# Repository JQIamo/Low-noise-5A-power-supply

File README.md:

# Low-noise-5A-power-supply
5A low noise +-15 V power supply for Eurocard boxes

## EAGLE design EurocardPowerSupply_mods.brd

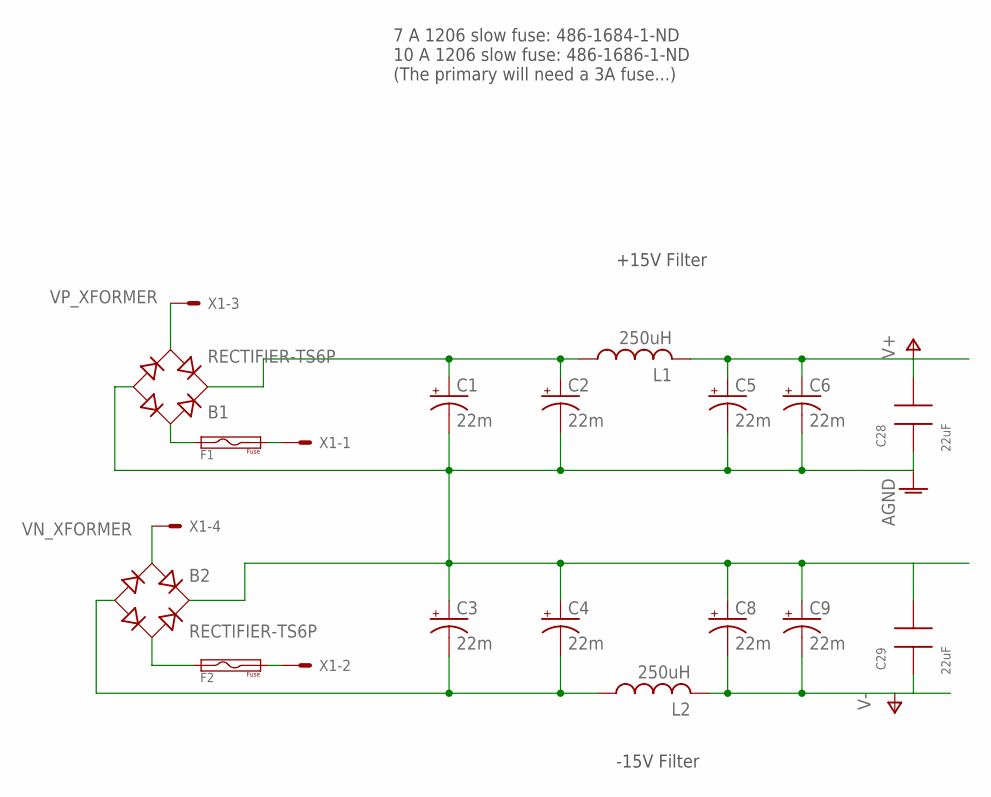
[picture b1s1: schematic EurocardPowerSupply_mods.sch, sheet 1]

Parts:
B1, B2: RECTIFIER-TS6P; TS6P
C1, C2, C3, C4, C5, C6, C8, C9: 22m; EB35D
C28, C29: 22uF; 1206; DIGIKEY 445-8045-1-ND
F1, F2: FUSE1206; DIGIKEY 486-1686-1-ND
L1, L2: 250uH; 5721-RC
X1: 5566-4

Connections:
AGND: B1.-, B2.+, C1.-, C2.-, C3.+, C4.+, C5.-, C6.-, C8.+, C9.+, C28.1, C29.2; also elsewhere on the board
unnamed: B1.AC1, F1.1
unnamed: F1.2, X1.1
unnamed: F2.2, X1.2
unnamed: B2.AC2, F2.1
V+: C5.+, C6.+, C28.2, L1.P$2 (2); also elsewhere on the board
V-: C8.-, C9.-, C29.1, L2.P$2 (2); also elsewhere on the board
VN_RECT: B2.-, C3.-, C4.-, L2.P$1 (1); also elsewhere on the board
VN_XFORMER: B2.AC1, X1.4
VP_RECT: B1.+, C1.+, C2.+, L1.P$1 (1); also elsewhere on the board
VP_XFORMER: B1.AC2, X1.3

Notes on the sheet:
-15V Filter
+15V Filter
7 A 1206 slow fuse: 486-1684-1-ND 10 A 1206 slow fuse: 486-1686-1-ND (The primary will need a 3A fuse...)

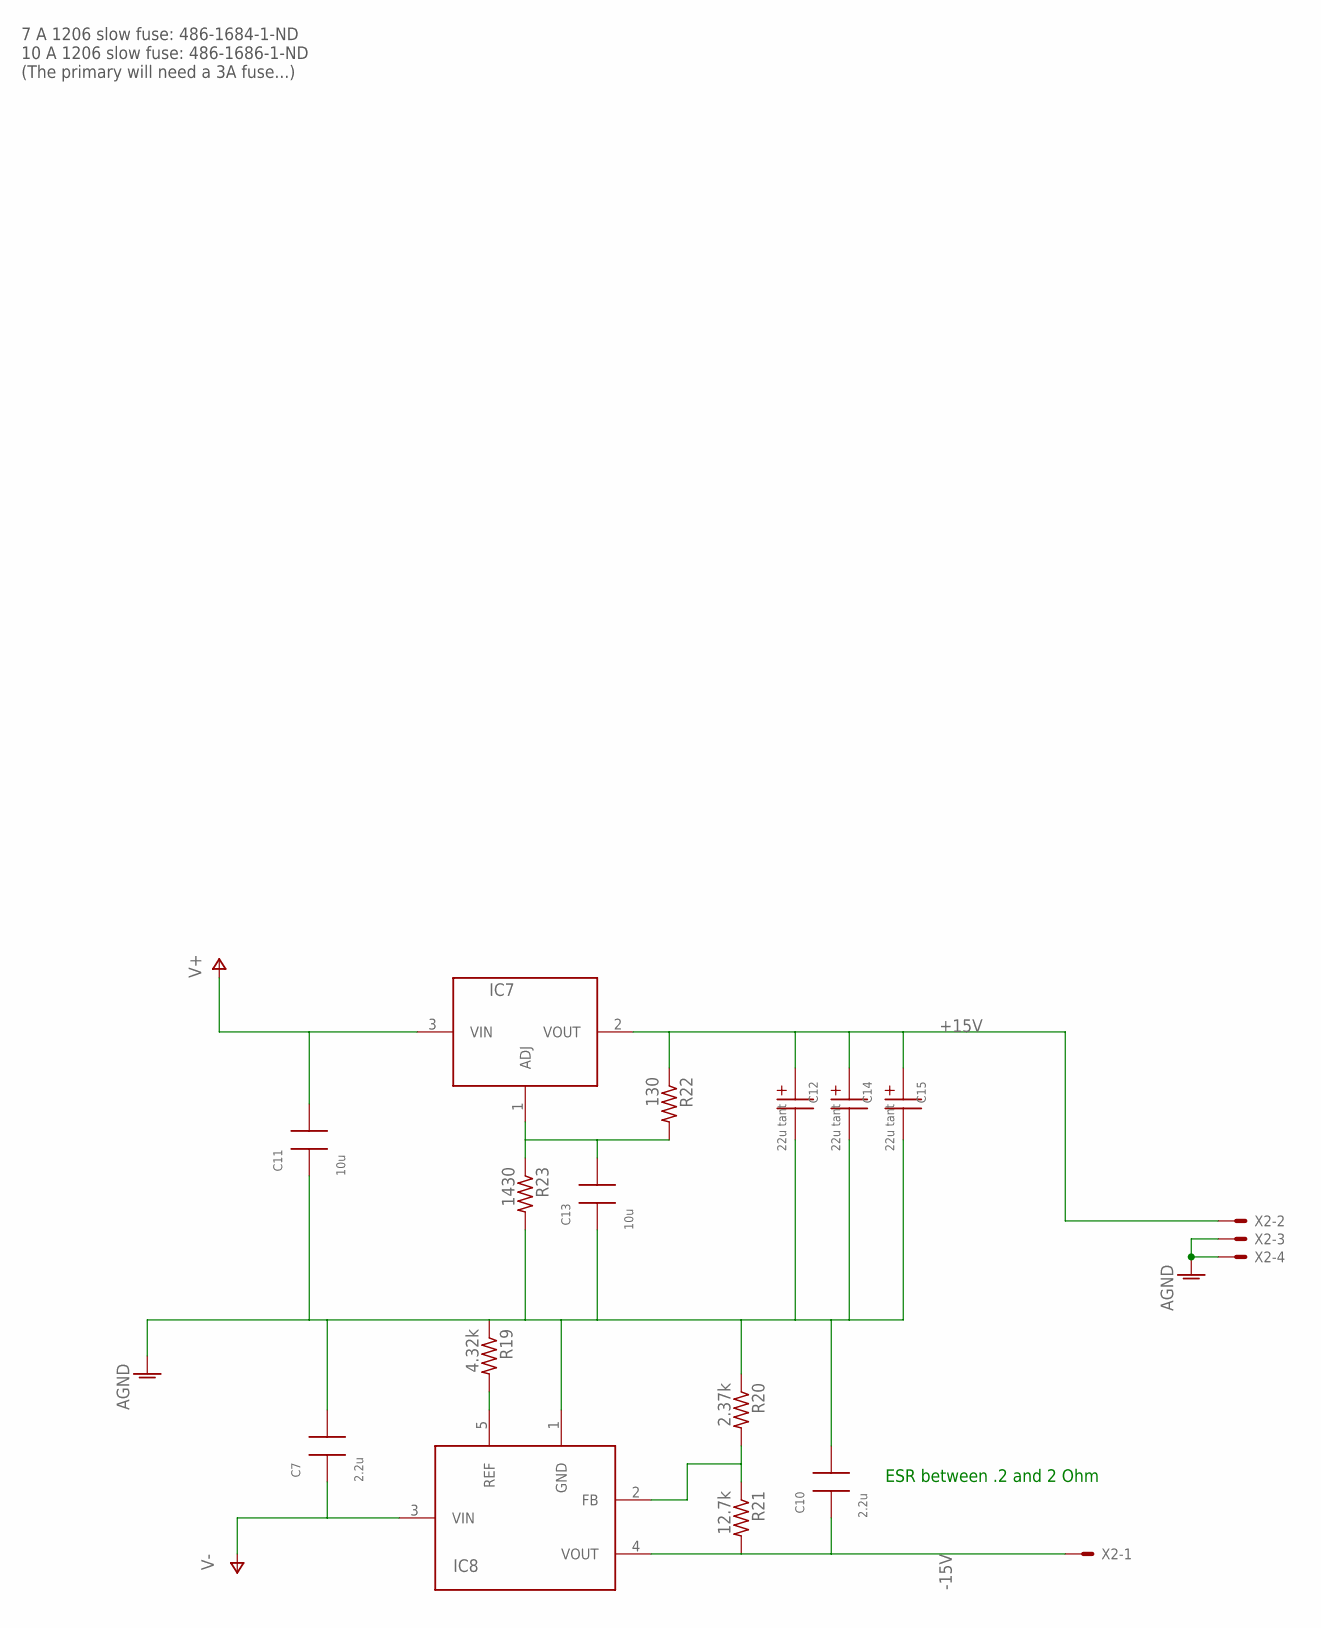
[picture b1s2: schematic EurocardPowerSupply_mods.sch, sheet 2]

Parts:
C7, C10: 2.2u; 1206; DIGIKEY 399-1249-1-ND
C11, C13: 10u; 1206; DIGIKEY 399-1249-1-ND
C12, C14, C15: 22u tant; 1206P; DIGIKEY 399-1249-1-ND
IC7: LM1084TO220; T03B
IC8: LT1185TO220/INLINE; T05A
R19: 4.32k; R1206; DIGIKEY 541-1.5KECT-ND
R20: 2.37k; R1206; DIGIKEY 541-1.5KECT-ND
R21: 12.7k; R1206; DIGIKEY 541-1.5KECT-ND
R22: 130; R1206; DIGIKEY 541-1.5KECT-ND
R23: 1430; R1206; DIGIKEY 541-1.5KECT-ND
X2: 5566-4

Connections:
+15V: C12.1, C14.1, C15.1, IC7.2 (VOUT), R22.1, X2.2
-15V: C10.1, IC8.4 (VOUT), R21.2, X2.1
AGND: C7.2, C10.2, C11.1, C12.2, C13.1, C14.2, C15.2, IC8.1 (GND), R19.1, R20.1, R23.2, X2.3, X2.4; also elsewhere on the board
unnamed: IC8.2 (FB), R20.2, R21.1
unnamed: C13.2, IC7.1 (ADJ), R22.2, R23.1
unnamed: IC8.5 (REF), R19.2
V+: C11.2, IC7.3 (VIN); also elsewhere on the board
V-: C7.1, IC8.3 (VIN); also elsewhere on the board

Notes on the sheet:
7 A 1206 slow fuse: 486-1684-1-ND 10 A 1206 slow fuse: 486-1686-1-ND (The primary will need a 3A fuse...)
ESR between .2 and 2 Ohm

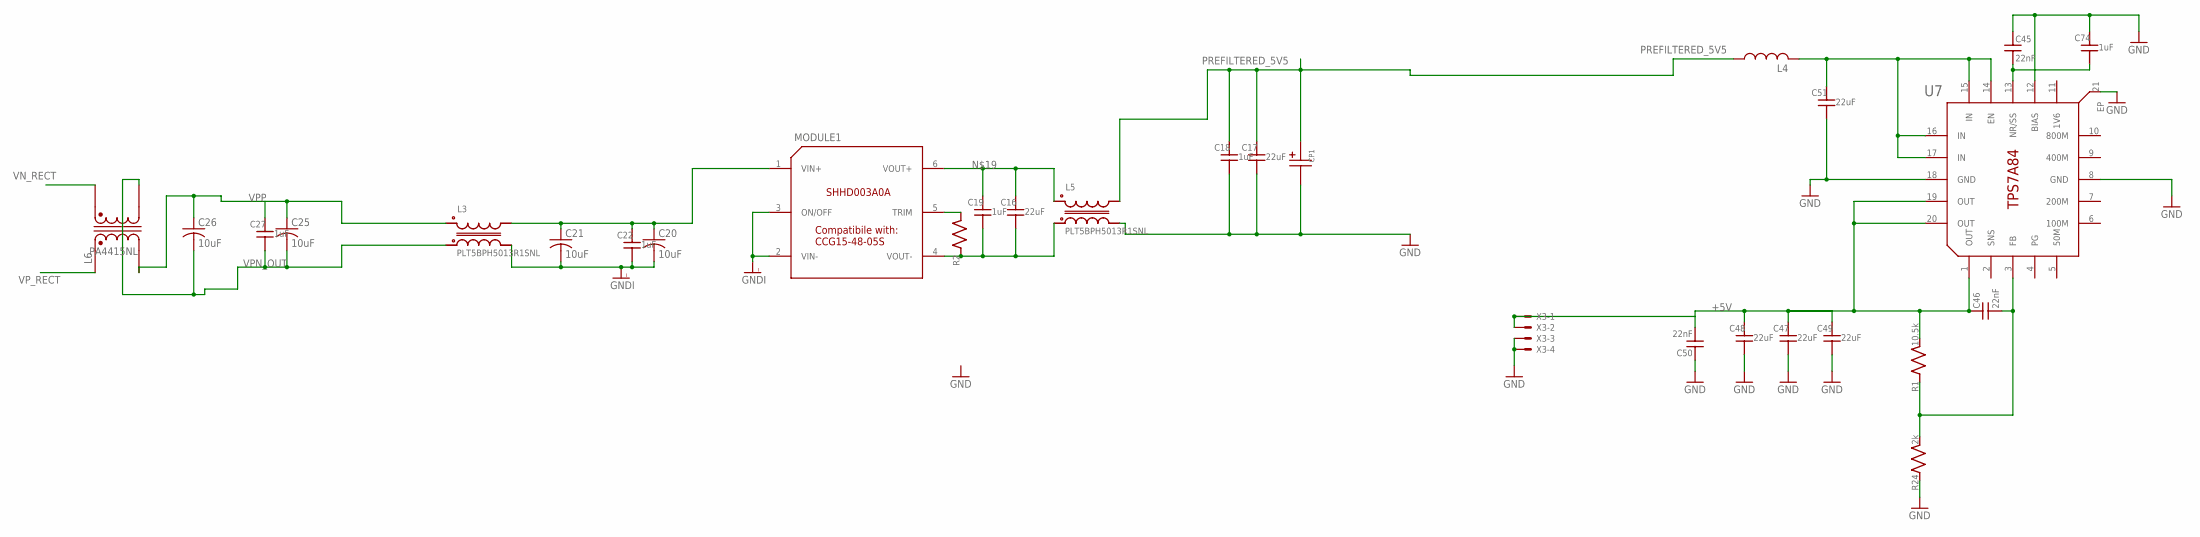
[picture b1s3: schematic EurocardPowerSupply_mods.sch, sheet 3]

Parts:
C16, C17, C47, C48, C49, C51: 22uF; C_MLCC_0805; DIGIKEY 445-9112-1-ND
C18, C19, C22, C27, C74: 1uF; C_MLCC_0805; DIGIKEY 587-5018-1-ND
C20, C21, C25, C26: 10uF; C2220K; DIGIKEY 445-7947-1-ND
C45, C46, C50: 22nF; C_MLCC_0306; DIGIKEY 490-4317-1-ND
CP1: CAP-POLPANASONIC_F; PANASONIC_F
L3, L5: PLT5BPH5013R1SNL; MURATA_CM_CHOKE_PLT5BPH_SERIES; MPN PLT5BPH5013R1SNL; DIGIKEY 490-10979-1-ND
L4: MURATA_NFZ5BBW100LN10L; MURATA_1MHZ_3A_FERRITE; DIGIKEY 490-12168-1-ND
L6: PA4415NL
MODULE1: GE_SHHD003A0A; GE_SHHD003A0A_THROUGH_HOLE; DIGIKEY 285-2609-ND
R1: 10.5k; R_0805; DIGIKEY 10.5k
R2: R_SMDR0805; R_0805
R24: 2k; R_0805; DIGIKEY RR12P2.0KDCT-ND
U7: TEXAS_INSTRUMENTS_TPS7A84; S-PVQFN-N20; DIGIKEY 296-43749-1-ND
X3: 5566-4

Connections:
+5V: C46.P$1 (1), C47.P$1 (1), C48.P$1 (1), C49.P$1 (1), C50.P$2 (2), R1.P$2 (2), U7.1 (OUT), U7.19 (OUT), U7.20 (OUT), X3.1, X3.2
GND: C17.P$2 (2), C18.P$2 (2), C45.P$1 (1), C47.P$2 (2), C48.P$2 (2), C49.P$2 (2), C50.P$1 (1), C51.P$2 (2), C74.P$1 (1), CP1.-, L5.P$3 (3), R24.P$1 (1), U7.8 (GND), U7.12 (BIAS), U7.18 (GND), U7.21 (EP), X3.3, X3.4
GNDI: C20.2, C21.2, C22.P$2 (2), L3.P$3 (3), MODULE1.2 (VIN-), MODULE1.3 (ON/OFF)
unnamed: C16.P$2 (2), C19.P$2 (2), L5.P$4 (1), MODULE1.4 (VOUT-), R2.P$1 (1)
unnamed: MODULE1.5 (TRIM), R2.P$2 (2)
unnamed: C16.P$1 (1), C19.P$1 (1), L5.P$1 (2), MODULE1.6 (VOUT+)
unnamed: C45.P$2 (2), C74.P$2 (2), U7.13 (NR/SS)
unnamed: C46.P$2 (2), R1.P$1 (1), R24.P$2 (2), U7.3 (FB)
unnamed: C51.P$1 (1), L4.P$2 (2), U7.14 (EN), U7.15 (IN), U7.16 (IN), U7.17 (IN)
PREFILTERED_5V5: C17.P$1 (1), C18.P$1 (1), CP1.+, L4.P$1 (1), L5.P$2 (4)
VN_RECT: L6.2; also elsewhere on the board
VPN_OUT: C25.2, C26.2, C27.P$2 (2), L3.P$4 (1), L6.3 (4)
VPP: C25.1, C26.1, C27.P$1 (1), L3.P$1 (2), L6.4 (3)
VPPI: C20.1, C21.1, C22.P$1 (1), L3.P$2 (4), MODULE1.1 (VIN+)
VP_RECT: L6.1; also elsewhere on the board

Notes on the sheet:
Compatibile with: CCG15-48-05S

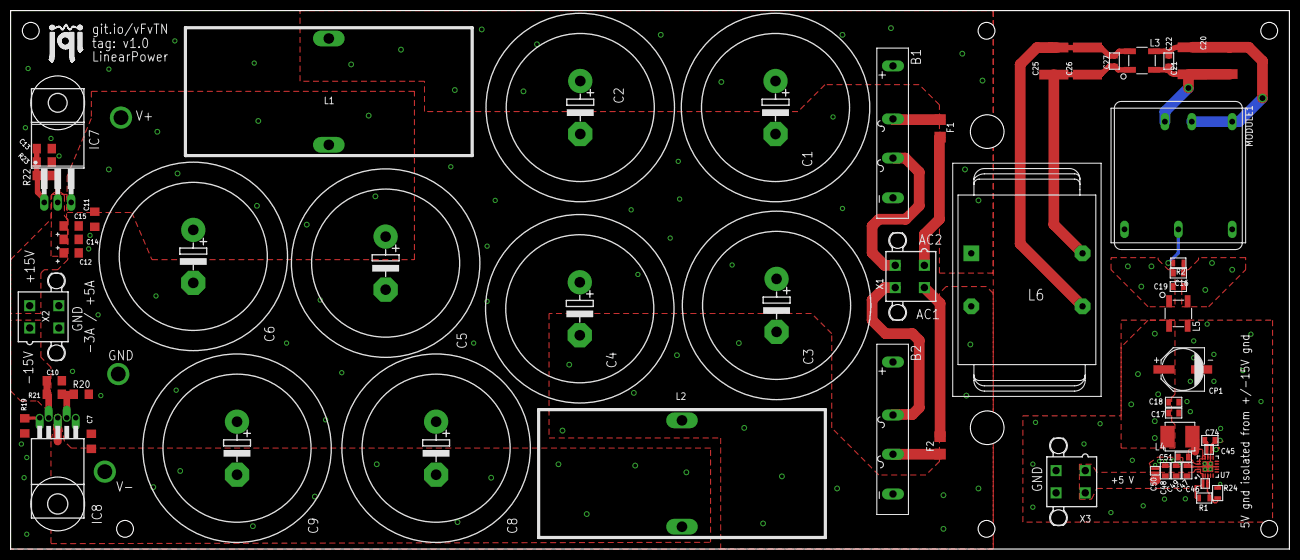
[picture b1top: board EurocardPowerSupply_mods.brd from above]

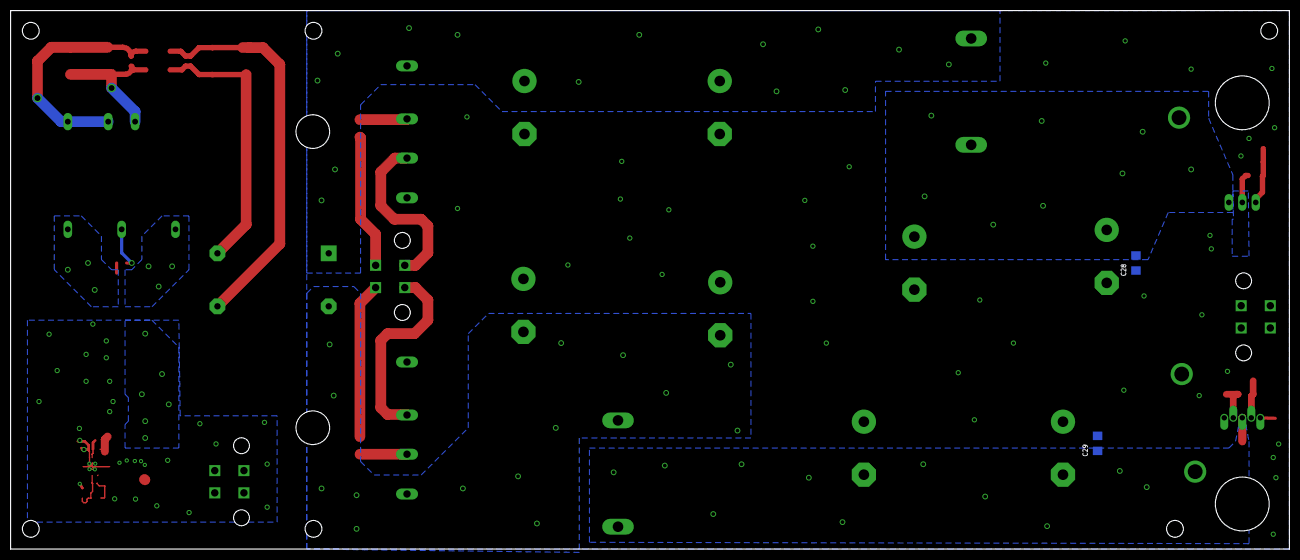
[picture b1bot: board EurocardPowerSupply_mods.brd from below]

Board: 2 copper layers, 241.3 x 101.6 mm, 62 parts (2 on the bottom side), 29 nets.

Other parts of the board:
U$1: JQI_LOGO_POSITIVE-SILKSCREEN

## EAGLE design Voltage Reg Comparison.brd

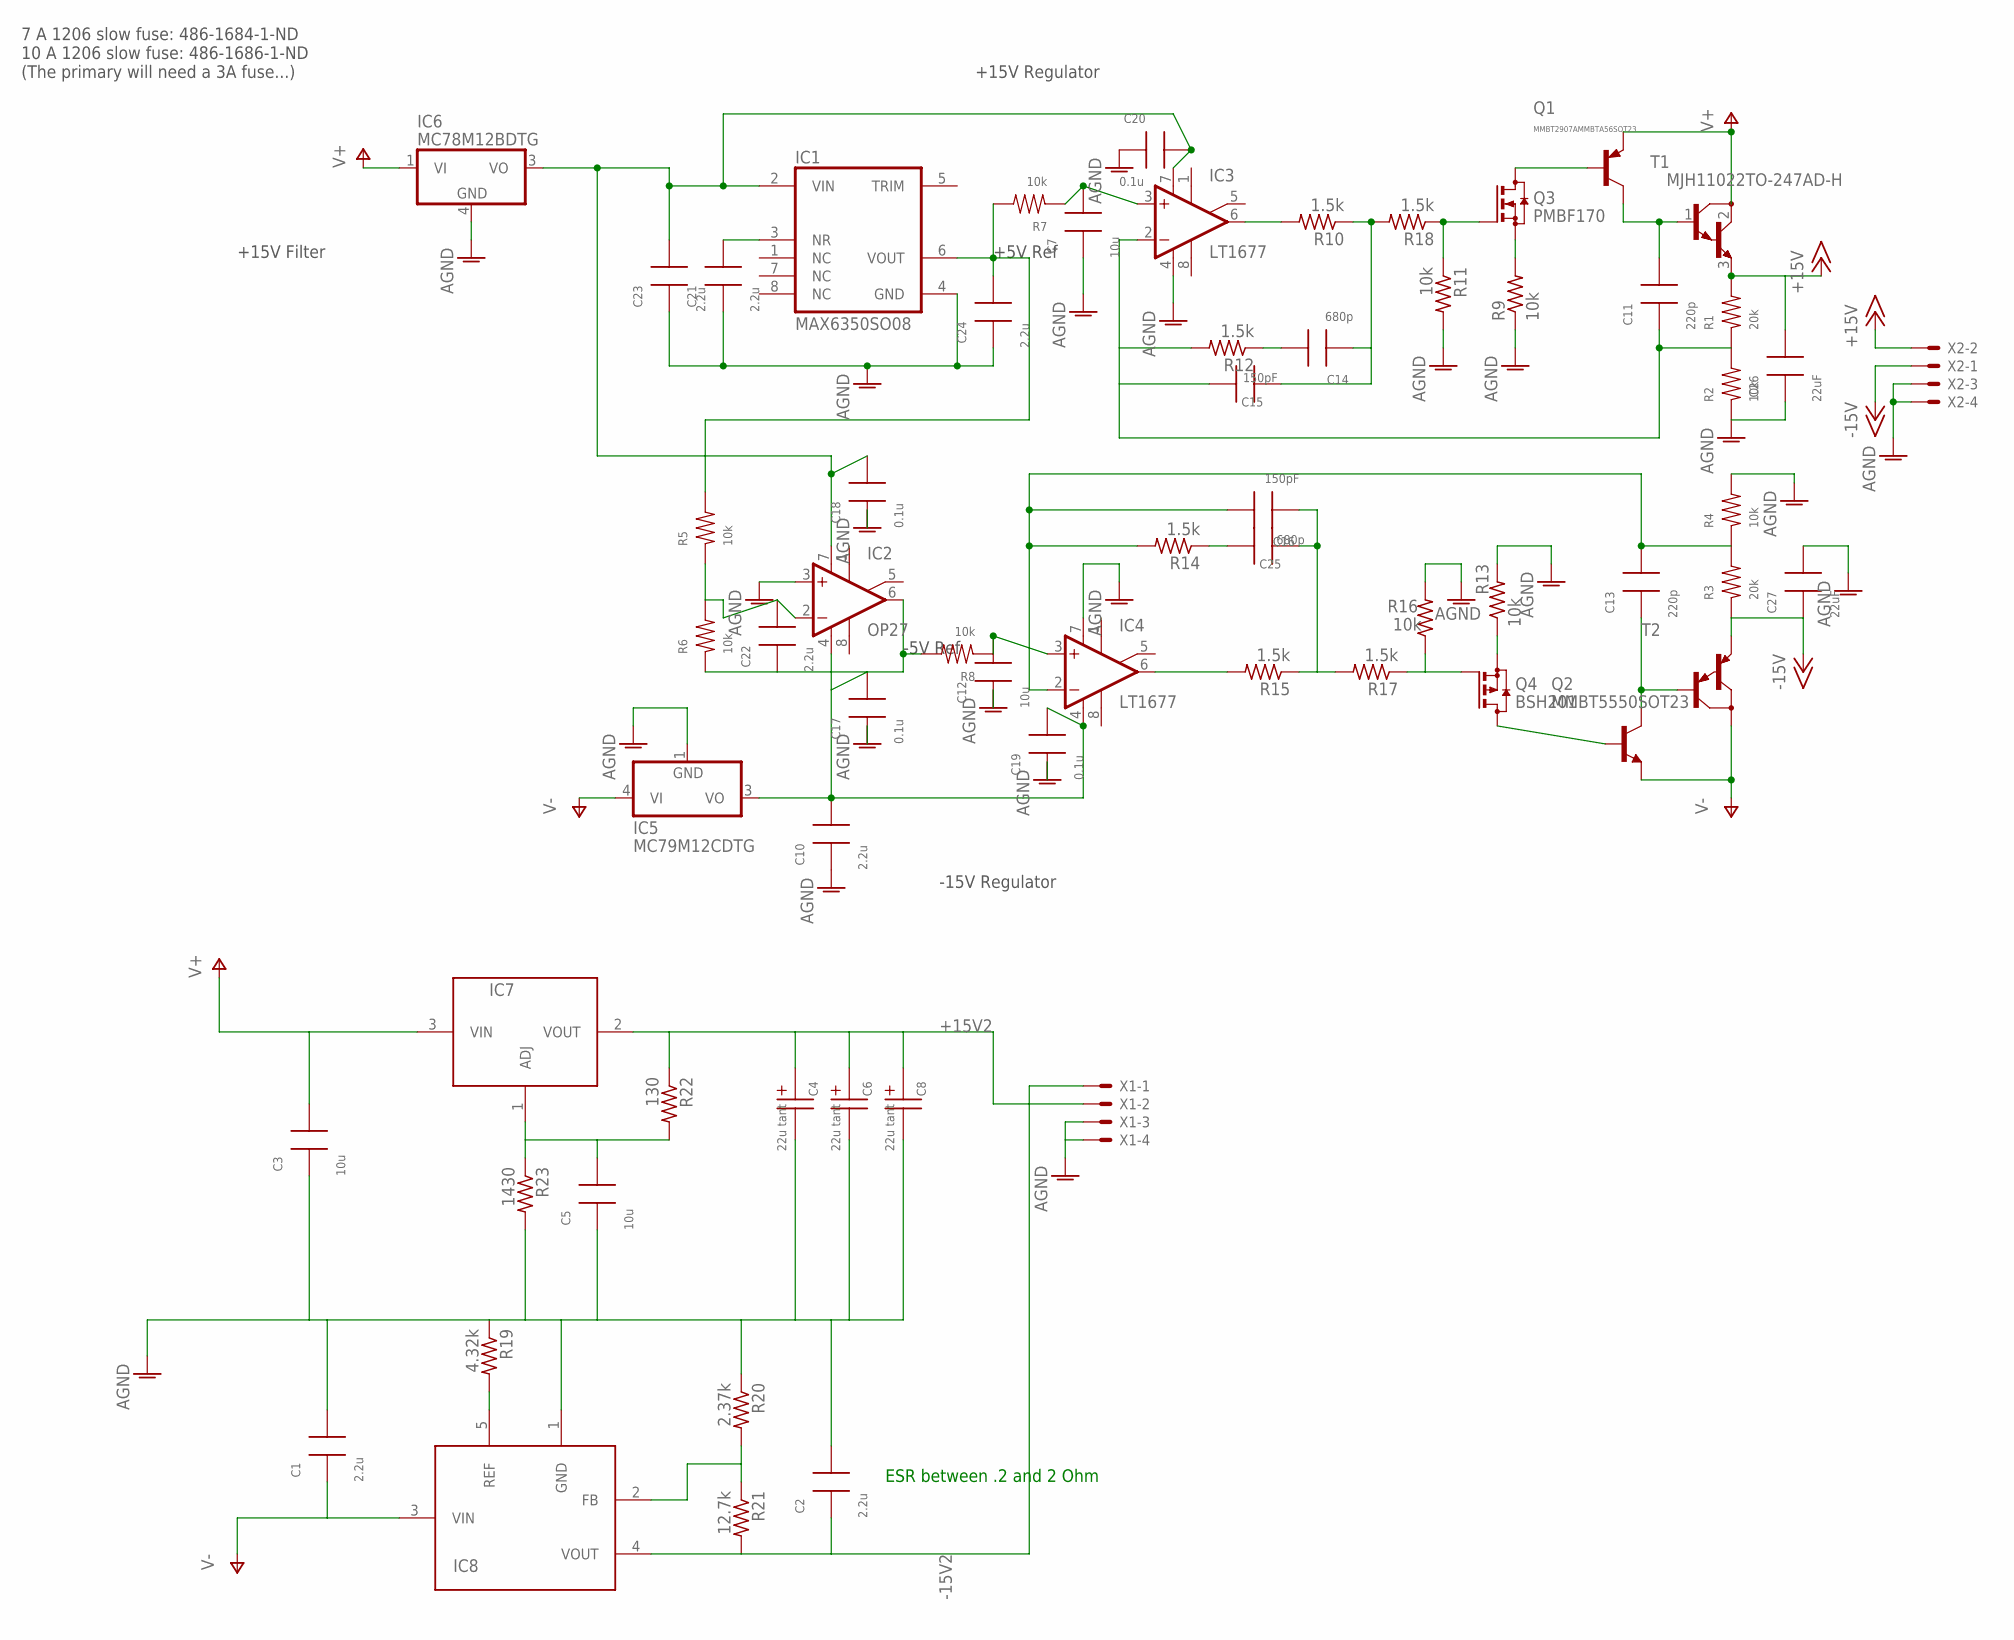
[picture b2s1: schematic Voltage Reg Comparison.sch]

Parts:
C1, C2: 2.2u; 1206; DIGIKEY 399-1249-1-ND
C3, C5: 10u; 1206; DIGIKEY 399-1249-1-ND
C4, C6, C8: 22u tant; 1206P; DIGIKEY 399-1249-1-ND
C7, C12: 10u; 1206; DIGIKEY 445-12883-2-ND
C10, C21, C22, C23, C24: 2.2u; 1206; DIGIKEY 587-2402-1-ND
C11, C13: 220p; 1206; DIGIKEY 1276-1166-1-ND
C14, C25: 680p; 1206; DIGIKEY 399-8209-1-ND
C15, C16: 150pF; 1206
C17, C18, C19, C20: 0.1u; 1206; DIGIKEY 399-1249-1-ND
C26, C27: 22uF; 1206; DIGIKEY 445-8045-1-ND
IC1: MAX6350SO08; SO08
IC2: OP27; SO08; DIGIKEY OP27GSZ-REEL7CT-ND
IC3, IC4: LT1677; SO08; DIGIKEY LT1677CS8#PBF-ND
IC5: MC79M12CDTG; DPACK_3; DIGIKEY MC79M12CDTGOS-ND
IC6: MC78M12BDTG; DPACK_3; DIGIKEY MC78M12BDTGOS-ND
IC7: LM1084TO220; T03B
IC8: LT1185TO220/INLINE; T05A
Q1: MMBT2907AMMBTA56SOT23; SOT23
Q2: MMBT5550SOT23; SOT23; DIGIKEY MMBT5550CT-ND
Q3: PMBF170; SOT23; DIGIKEY MMBT2907AFSCT-ND
Q4: BSH201; SOT23; DIGIKEY 568-6217-1-ND
R1, R3: 20k; 1206; DIGIKEY RMCF1206FT20K0CT-ND
R2, R4, R5, R6, R7, R8: 10k; 1206; DIGIKEY RNCP1206FTD10K0CT-ND
R9, R13: 10k; R1206; DIGIKEY RNCP1206FTD10K0CT-ND
R10, R12, R14, R15, R17, R18: 1.5k; R1206; DIGIKEY 541-1.5KECT-ND
R11, R16: 10k; R1206; DIGIKEY 541-1.5KECT-ND
R19: 4.32k; R1206; DIGIKEY 541-1.5KECT-ND
R20: 2.37k; R1206; DIGIKEY 541-1.5KECT-ND
R21: 12.7k; R1206; DIGIKEY 541-1.5KECT-ND
R22: 130; R1206; DIGIKEY 541-1.5KECT-ND
R23: 1430; R1206; DIGIKEY 541-1.5KECT-ND
T1: MJH11022TO-247AD-H; TO-247AD-H
T2: MJH11021TO-247AD-H; TO-247AD-H
X1, X2: 5566-4RA; 5566-4-RA

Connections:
+12V: C18.2, C20.2, C23.2, IC1.2 (VIN), IC2.7 (V+), IC3.7 (V+), IC6.3 (VO)
+15V: C26.2, R1.2, T1.3 (E), X2.2
+15V2: C4.1, C6.1, C8.1, IC7.2 (VOUT), R22.1, X1.2
-12V: C10.2, C17.2, C19.2, IC2.4 (V-), IC4.4 (V-), IC5.3 (VO)
-15V: C27.1, R3.1, T2.3 (E), X2.1
-15V2: C2.1, IC8.4 (VOUT), R21.2, X1.1
AGND: C1.2, C2.2, C3.1, C4.2, C5.1, C6.2, C7.1, C8.2, C10.1, C12.1, C17.1, C18.1, C19.1, C20.1, C21.1, C23.1, C24.1, C26.1, C27.2, IC1.4 (GND), IC2.3 (+IN), IC3.4 (V-), IC4.7 (V+), IC5.1 (GND), IC6.4 (GND), IC8.1 (GND), R2.1, R4.2, R9.1, R11.2, R13.2, R16.2, R19.1, R20.1, R23.2, X1.3, X1.4, X2.3, X2.4
unnamed: IC8.2 (FB), R20.2, R21.1
unnamed: C5.2, IC7.1 (ADJ), R22.2, R23.1
unnamed: C21.2, IC1.3 (NR)
unnamed: C24.2, IC1.6 (VOUT), R5.2, R7.2
unnamed: C14.2, R12.1
unnamed: C13.1, Q2.3 (C), T2.1 (B)
unnamed: IC3.6 (OUT), R10.2
unnamed: Q4.1 (G), R16.1, R17.1
unnamed: C11.2, Q1.3 (C), T1.1 (B)
unnamed: C22.2, IC2.2 (-IN), R5.1, R6.2
unnamed: C22.1, IC2.6 (OUT), R6.1, R8.2
unnamed: Q4.2 (S), R13.1
unnamed: C11.1, C15.2, IC3.2 (-IN), R1.1, R2.2, R12.2
unnamed: IC4.6 (OUT), R15.2
unnamed: C7.2, IC3.3 (+IN), R7.1
unnamed: Q2.1 (B), Q4.3 (D)
unnamed: C12.2, IC4.3 (+IN), R8.1
unnamed: IC8.5 (REF), R19.2
unnamed: C13.2, C16.2, IC4.2 (-IN), R3.2, R4.1, R14.2
unnamed: Q3.1 (G), R11.1, R18.1
unnamed: C25.2, R14.1
unnamed: C16.1, C25.1, R15.1, R17.2
unnamed: Q1.1 (B), Q3.3 (D)
unnamed: Q3.2 (S), R9.2
unnamed: C14.1, C15.1, R10.1, R18.2
V+: IC6.1 (VI), Q1.2 (E), T1.2 (C)
V+2: C3.2, IC7.3 (VIN)
V-: IC5.4 (VI), Q2.2 (E), T2.2 (C)
V-2: C1.1, IC8.3 (VIN)

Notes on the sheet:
+5V Ref
-5V Ref
+15V Regulator
-15V Regulator
+15V Filter
7 A 1206 slow fuse: 486-1684-1-ND 10 A 1206 slow fuse: 486-1686-1-ND (The primary will need a 3A fuse...)
ESR between .2 and 2 Ohm

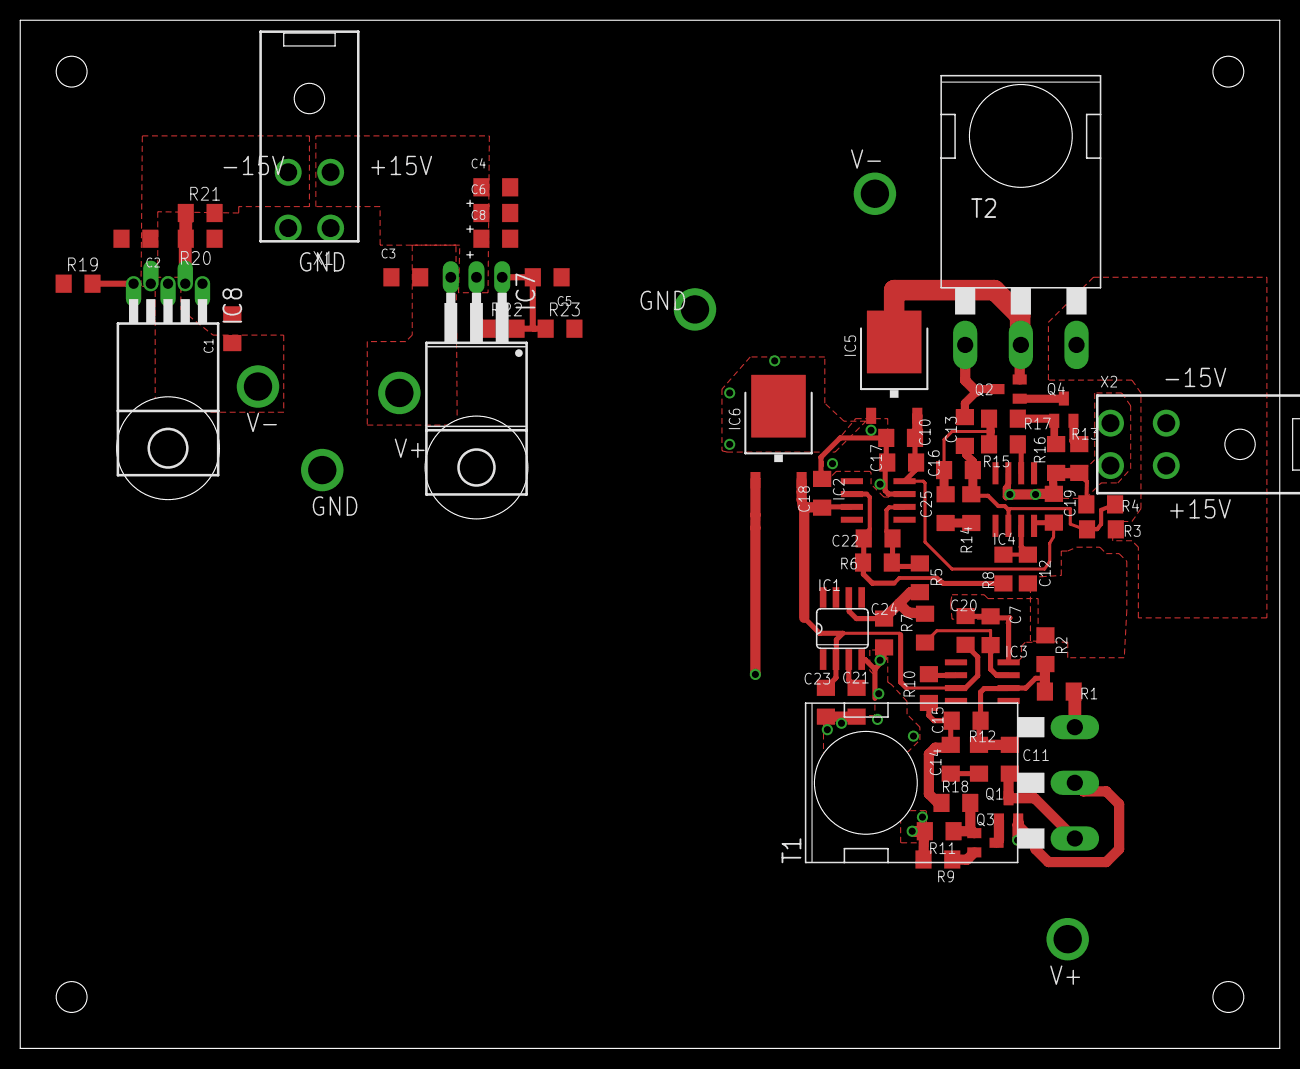
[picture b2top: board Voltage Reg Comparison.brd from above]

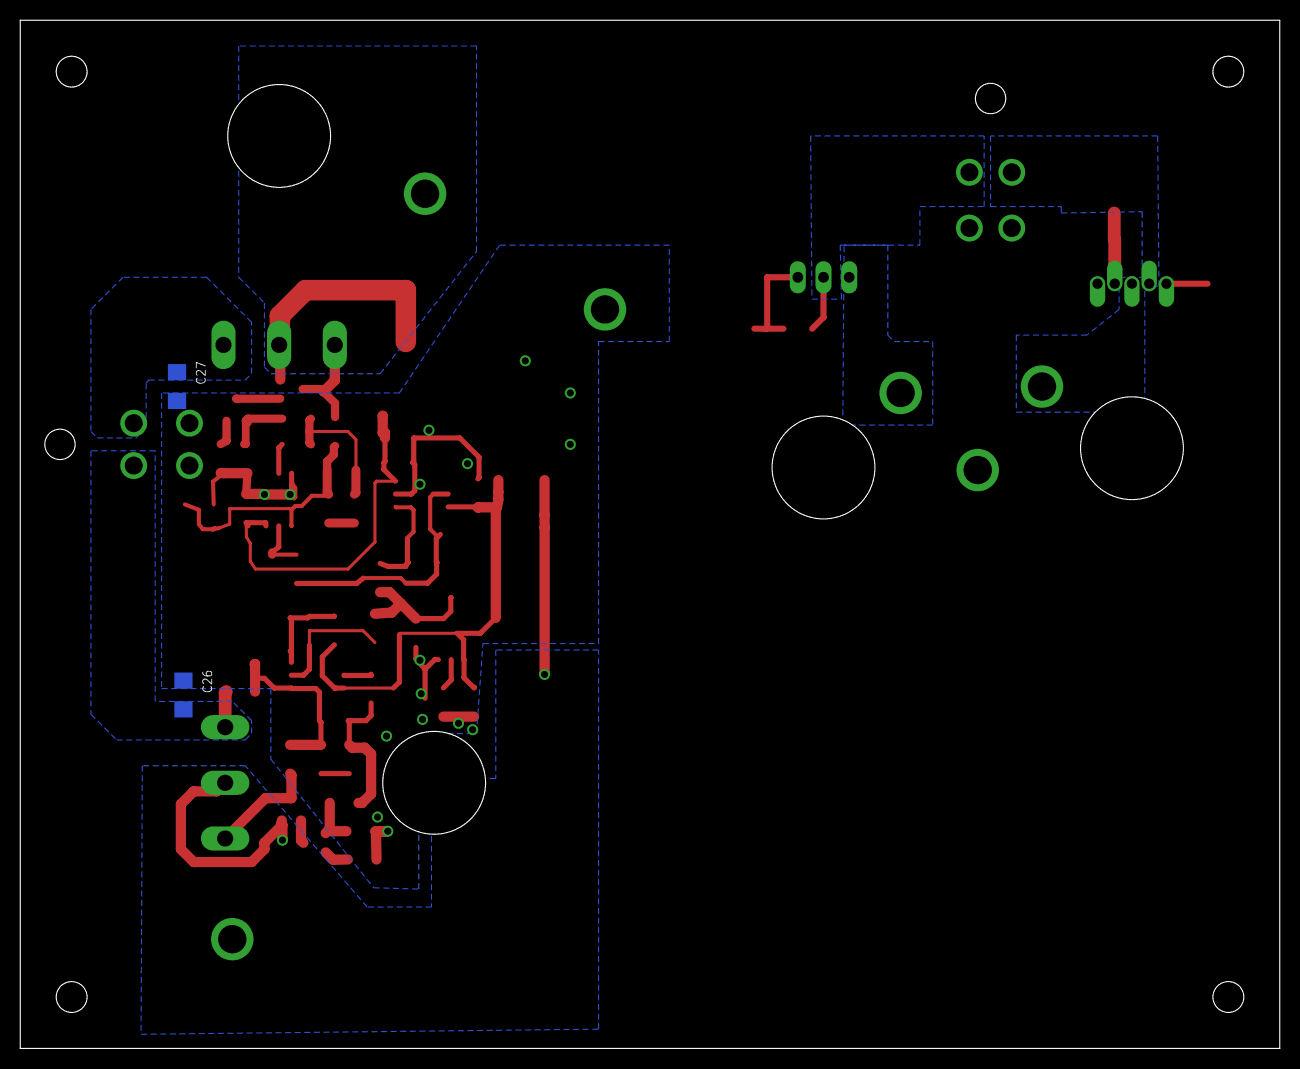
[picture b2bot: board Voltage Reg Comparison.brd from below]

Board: 4 copper layers, 124.5 x 101.6 mm, 65 parts (2 on the bottom side), 36 nets.

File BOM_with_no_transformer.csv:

"Qty";"Value";"Device";"Parts";"Description";"DIGIKEY";"VMAX";
"3";"";"5566-4RA";"X1, X2, X3";"Mini FIT connector 4 pol";"WM1352-ND";"";
"2";"";"FUSE1206";"F1, F2";"";"486-1686-1-ND";"";
"4";"0.1u";"CAP1206";"C17, C18, C19, C20";"SMT Capacitor";"399-1249-1-ND";"";
"8";"1.5k";"R-US_R1206";"R10, R11, R12, R14, R15, R16, R17, R18";"RESISTOR, American symbol";"541-1.5KECT-ND";"";
"5";"2.2u";"CAP1206";"C10, C21, C22, C23, C24";"SMT Capacitor";"587-2402-1-ND";"";
"2";"10k";"R-US_R1206";"R9, R13";"RESISTOR, American symbol";"RNCP1206FTD10K0CT-ND";"";
"6";"10k";"RES1206";"R2, R4, R5, R6, R7, R8";"SMT Resistor";"RNCP1206FTD10K0CT-ND";"";
"2";"10u";"CAP1206";"C7, C12";"SMT Capacitor";"445-12883-2-ND";"50";
"2";"20k";"RES1206";"R1, R3";"SMT Resistor";"RMCF1206FT20K0CT-ND";"";
"6";"22m";"CPOL-USEB35D";"C5, C6, C8, C9, C30, C31";"";"565-2880-ND";"";
"4";"22uF";"CAP1206";"C26, C27, C28, C29";"SMT Capacitor";"445-8045-1-ND";"";
"2";"220p";"CAP1206";"C11, C13";"SMT Capacitor";"1276-1166-1-ND";"";
"2";"250uH";"INDUCTOR5721-RC";"L1, L2";"";"M8725-ND";"";
"2";"680p";"CAP1206";"C14, C25";"SMT Capacitor";"399-8209-1-ND";"";
"4";"4700u";"CPOL-USE7.5-18";"C1, C2, C3, C4";"";"495-6089-ND";"";
"1";"BSH201";"BSH201";"Q4";"P-CHANNEL MOS FET";"568-6217-1-ND";"";
"2";"DNP";"CAP1206";"C15, C16";"SMT Capacitor";"";"";
"2";"LT1677";"OPAMP-SO";"IC3, IC4";"Basic Op Amp. Be sure to check actual pinout of your device, and";"LT1677CS8#PBF-ND";"";
"1";"MAX6350SO08";"MAX6350SO08";"IC1";"VOLATAGE REFERENCE";"MAX6350CSA+-ND";"";
"1";"MC78M12BDTG";"MC78M12BDTG";"IC6";"500 mA Positive Voltage Regulators";"MC78M12BDTGOS-ND";"";
"1";"MC79M12CDTG";"MC79M12CDTG";"IC5";"500 mA Negative Voltage Regulators";"MC79M12CDTGOS-ND";"";
"1";"MJH11021TO-247AD-H";"MJH11021TO-247AD-H";"T2";"PNP POWER DARLINGTON TRANSISTOR";"MJH11021GOS-ND";"";
"1";"MJH11022TO-247AD-H";"MJH11022TO-247AD-H";"T1";"NPN POWER DARLINGTON TRANSISTOR";"MJH11022GOS-ND";"";
"1";"MMBT2907AMMBTA56SOT23";"MMBT2907AMMBTA56SOT23";"Q1";"PNP Transistor";"MMBT2907AFSCT-ND";"";
"1";"MMBT5550SOT23";"MMBT5550SOT23";"Q2";"NPN Transistor";"MMBT5550CT-ND";"";
"1";"OP27";"OPAMP-SO";"IC2";"Basic Op Amp. Be sure to check actual pinout of your device, and";"OP27GSZ-REEL7CT-ND";"";
"1";"PMBF170";"PMBF170";"Q3";"N-CHANNEL MOS FET";"MMBT2907AFSCT-ND";"";
"2";"RECTIFIER-TS6P";"RECTIFIER-TS6P";"B1, B2";"Rectifier";"DFB2005-ND";"";

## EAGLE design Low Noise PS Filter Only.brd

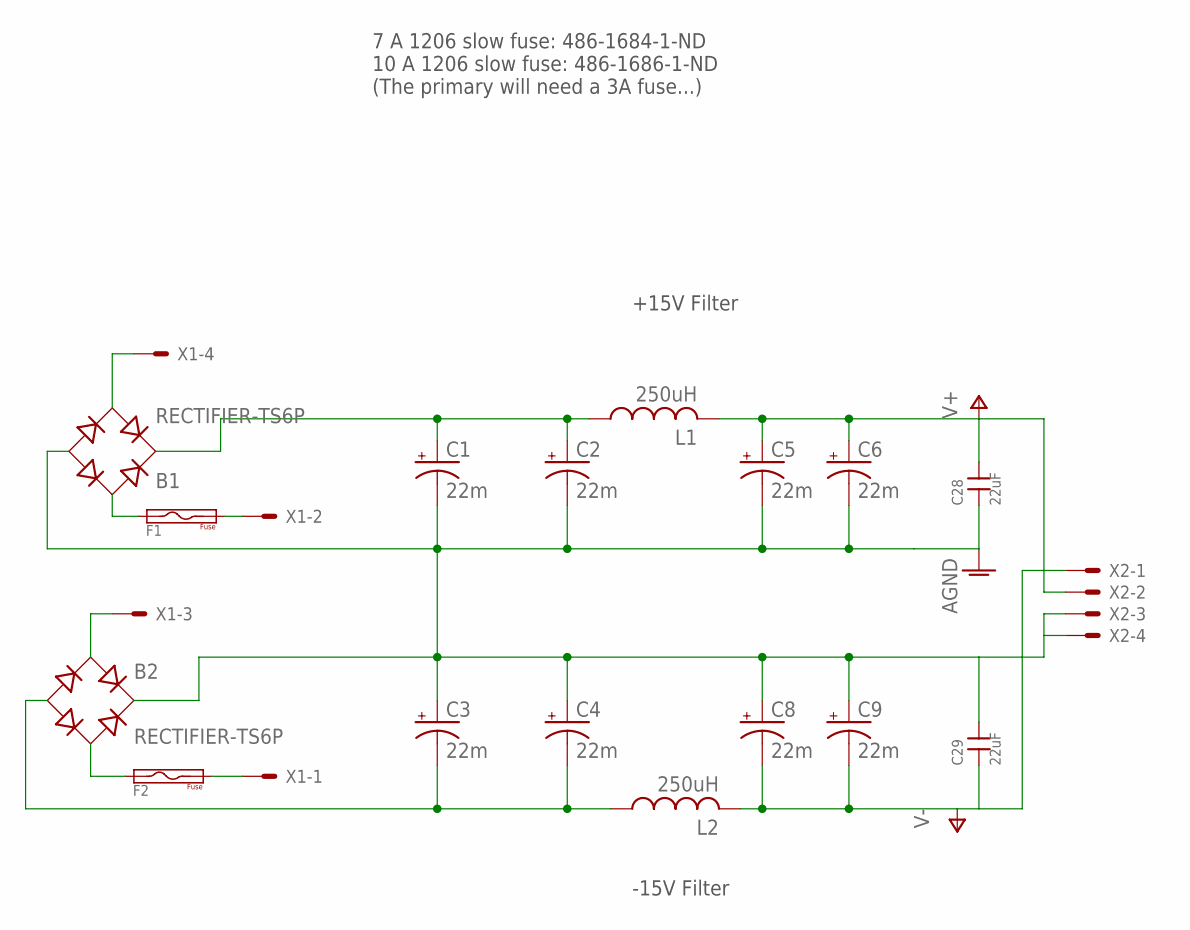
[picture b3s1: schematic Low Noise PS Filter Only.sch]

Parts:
B1, B2: RECTIFIER-TS6P; TS6P
C1, C2, C3, C4, C5, C6, C8, C9: 22m; EB35D
C28, C29: 22uF; 1206; DIGIKEY 445-8045-1-ND
F1, F2: FUSE1206; DIGIKEY 486-1686-1-ND
L1, L2: 250uH; 5721-RC
X1, X2: 5566-4

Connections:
AGND: B1.-, B2.+, C1.-, C2.-, C3.+, C4.+, C5.-, C6.-, C8.+, C9.+, C28.1, C29.2, X2.3, X2.4
unnamed: B1.AC1, F1.1
unnamed: B1.AC2, X1.4
unnamed: B1.+, C1.+, C2.+, L1.P$1 (1)
unnamed: B2.AC1, X1.3
unnamed: F1.2, X1.2
unnamed: F2.2, X1.1
unnamed: B2.-, C3.-, C4.-, L2.P$1 (1)
unnamed: B2.AC2, F2.1
V+: C5.+, C6.+, C28.2, L1.P$2 (2), X2.2
V-: C8.-, C9.-, C29.1, L2.P$2 (2), X2.1

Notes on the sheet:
-15V Filter
+15V Filter
7 A 1206 slow fuse: 486-1684-1-ND 10 A 1206 slow fuse: 486-1686-1-ND (The primary will need a 3A fuse...)

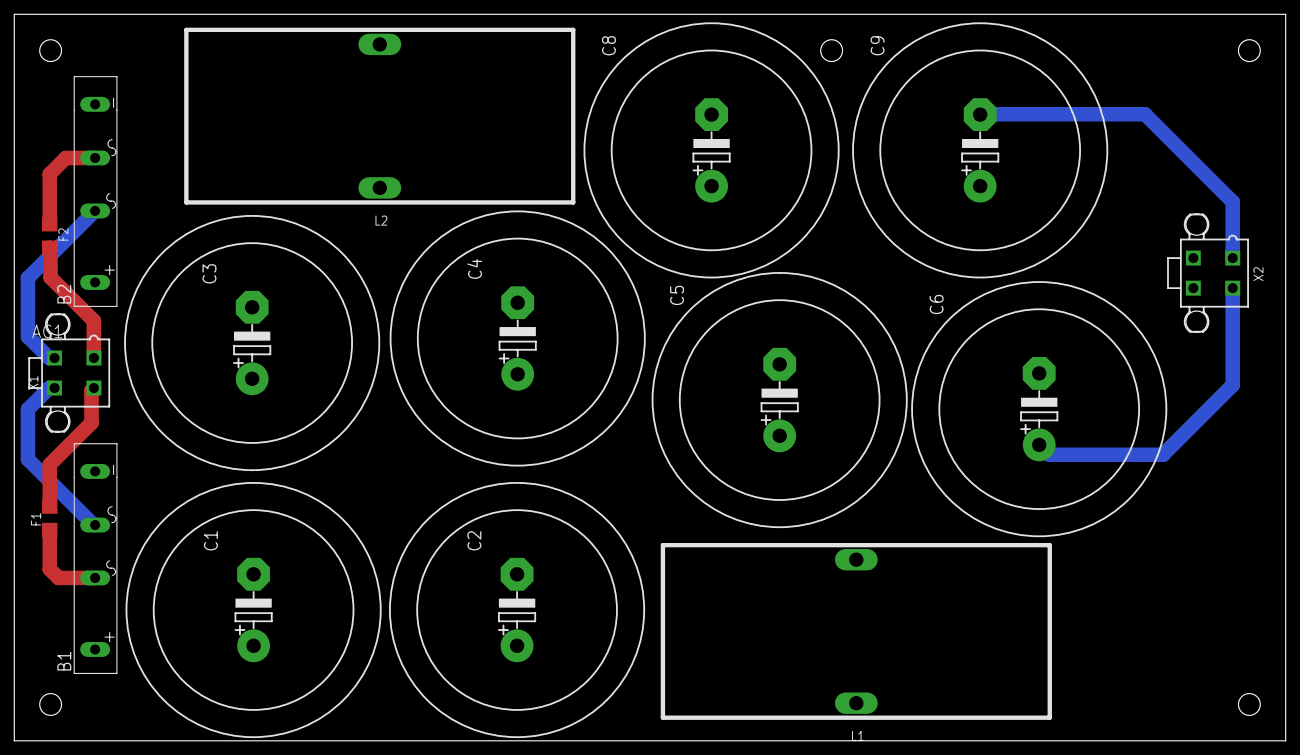
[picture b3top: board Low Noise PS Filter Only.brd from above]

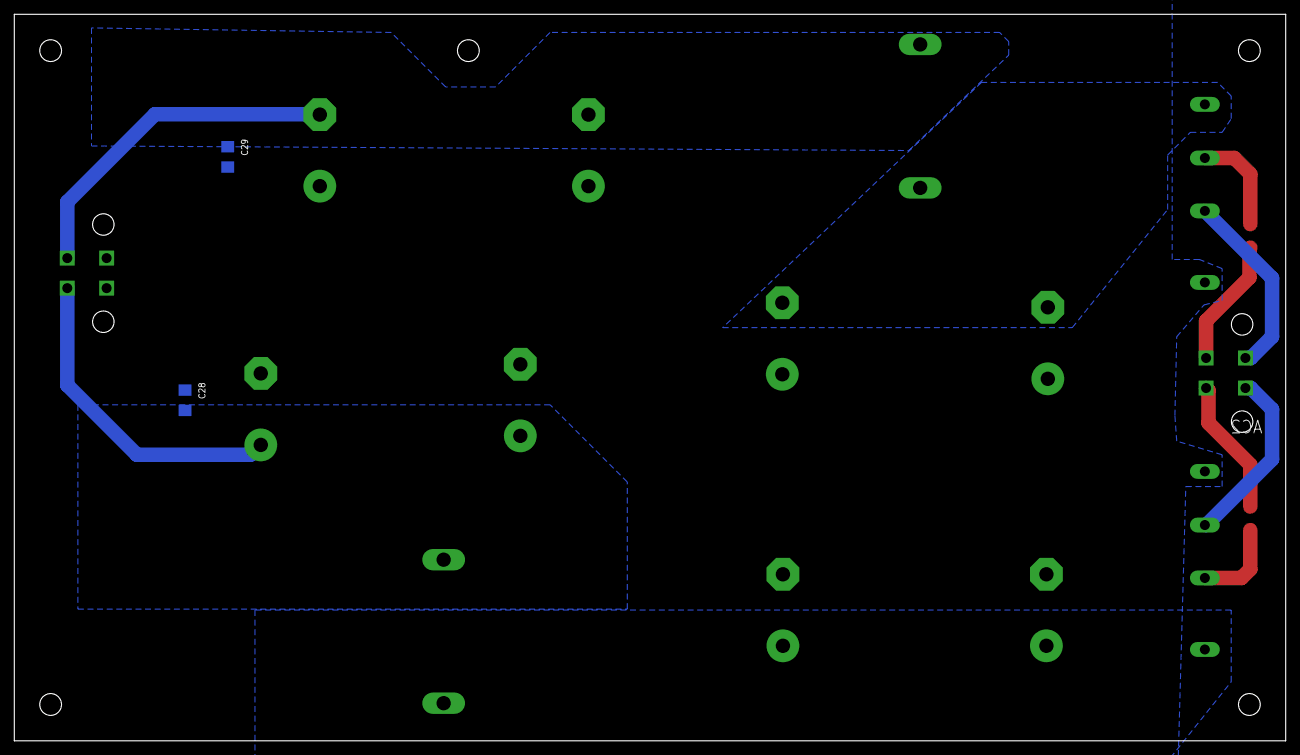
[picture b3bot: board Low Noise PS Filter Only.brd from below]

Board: 4 copper layers, 177.8 x 101.6 mm, 18 parts (2 on the bottom side), 11 nets.

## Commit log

2015-03-24 :tada: Added .gitattributes & .gitignore files
2015-03-24 Revert ":tada: Added .gitattributes & .gitignore files"
    This reverts commit ba0b8185cd7c8ab148a04d9a3679d0028e738854.
2015-03-24 Setting up the correct files and directories
2015-03-26 Intermediate version
    More work is still required
2015-04-02 Almost ready to print
    1) "cosmetic" adjustments needed (mainly increasing clearance for traces
    below SMD parts)
    2) component values need to be adjusted and chosen
    3) Silkscreen needs to be cleaned
2015-04-02 Creation of Readme file
2015-04-06 Version for LPKF printing.
    Most resistor/capacitor values are not final.
2015-04-14 BOM and part attributes adjusted
    This commit is not quite the final one: a performance test must be done
    before putting it into production. Also it might be useful to reorder
    part names to make assembly easy.
2015-04-21 Change in component values. Not final version!
    After assembling commit 290fa40aa6a372085 the board oscillates.
    Changing all DNP resistors and all 0 Ohm resistors to 1.5K Ohm makes the
    positive regulator stable under 6 Ohm load. The negative section is
    still unstable. Some final value adjustment will be required to ensure
    unconditional stability (with enough margin to account for the variation
    of capacitor values with temperature.
2015-04-21 Moved capacitor
    To avoid collision with transistor on the bottom side.
    Also a resistor has been rotated to reduce a trace lenght
2015-11-11 Swap pin 3/4 on Right Angle Molex, add Vreg ICs to library
2015-11-11 Add board to test a slightly different filter configuration
2015-11-11 Add board to compare custom V. Reg. vs IC solution
2017-11-13 v1.0 production
